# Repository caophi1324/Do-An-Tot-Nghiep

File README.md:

# Đồ Án Tốt Nghiệp

Workspace tổng hợp gồm 3 mảng chính: **phần cứng flight controller**, **mô phỏng bầy drone (SITL)** và **hệ thống nhận diện & bám sát khuôn mặt bằng AI**.

## Cấu trúc

| Thư mục | Nội dung |
|---|---|
| `Drone/` | Thiết kế phần cứng: flight controller `Drone ver2` (KiCad, BOM kèm LCSC), tay cầm điều khiển `Tay cam` (Altium), script tự động layout PCB (`Lib Kicad/arrange_*.py`), và 2 dự án tham khảo clone từ GitHub (`ESC_4in1_G071_1S3_SIZ200`, `Open-ESPilot`) |
| `drone_swarm_simulation_win11_wsl/` | Mô phỏng bầy drone ArduPilot SITL trên WSL: ứng dụng GCS (PySide6), engine ORCA/RVO2 + APF, điều khiển bằng gamepad, tích hợp Gazebo/RViz2. Hướng dẫn chạy: `HD_CHAY_MOPHONG_WIN11_WSL.md` |
| `StackMod/` | AI Face Tracking Studio: pipeline nhận diện khuôn mặt (YOLO + RetinaFace + EdgeFace + eDifFIQA), UI PySide6, REST API FastAPI, Docker. Hướng dẫn: `StackMod/README.md` |
| `fimware skill/` | Bộ 8 skill `.skill` (hướng dẫn vận hành drone: bringup, flight-safety, log-review, mavlink-review, sitl-sim, tuning...) kèm manifest SHA256 |

## Nội dung KHÔNG đưa lên repo (giữ trên máy local)

- `Drone/LIb AL/` — thư viện Altium cá nhân, các file >100 MB vượt giới hạn GitHub.
- `Drone/Lib Kicad/kicad-footprints`, `kicad-symbols-master` — thư viện chuẩn KiCad, cài lại qua KiCad hoặc clone từ [KiCad gitlab](https://gitlab.com/kicad).
- `drone_swarm_simulation_win11_wsl/ardupilot_wiki/` — clone wiki ArduPilot (~2.2 GB), xem [ArduPilot/ardupilot_wiki](https://github.com/ArduPilot/ardupilot_wiki).
- `StackMod/data/` — database + ảnh snapshots sinh khi chạy (chứa dữ liệu khuôn mặt).
- `StackMod/.venv/` — môi trường ảo Python.
- Các file `.zip`/`.rar` — bản nén trùng với nội dung đã giải nén.

## Ghi chú về các repo git cũ (`.git.bak`)

Các thư mục con trước đây có repo git riêng (`StackMod`, `Drone/ESC_4in1_G071_1S3_SIZ200`, `Drone/Open-ESPilot`, `Drone/Tay cam`) đã được gộp nội dung vào repo này; thư mục `.git` cũ được đổi tên thành `.git.bak` (bị gitignore). Muốn khôi phục repo riêng cũ, đổi tên `.git.bak` trở lại thành `.git`.

## Cài đặt nhanh StackMod

```bash
cd StackMod
python -m venv .venv && .venv\Scripts\activate
pip install -e .
python tools/download_models.py   # nếu chưa có models/*.onnx
```

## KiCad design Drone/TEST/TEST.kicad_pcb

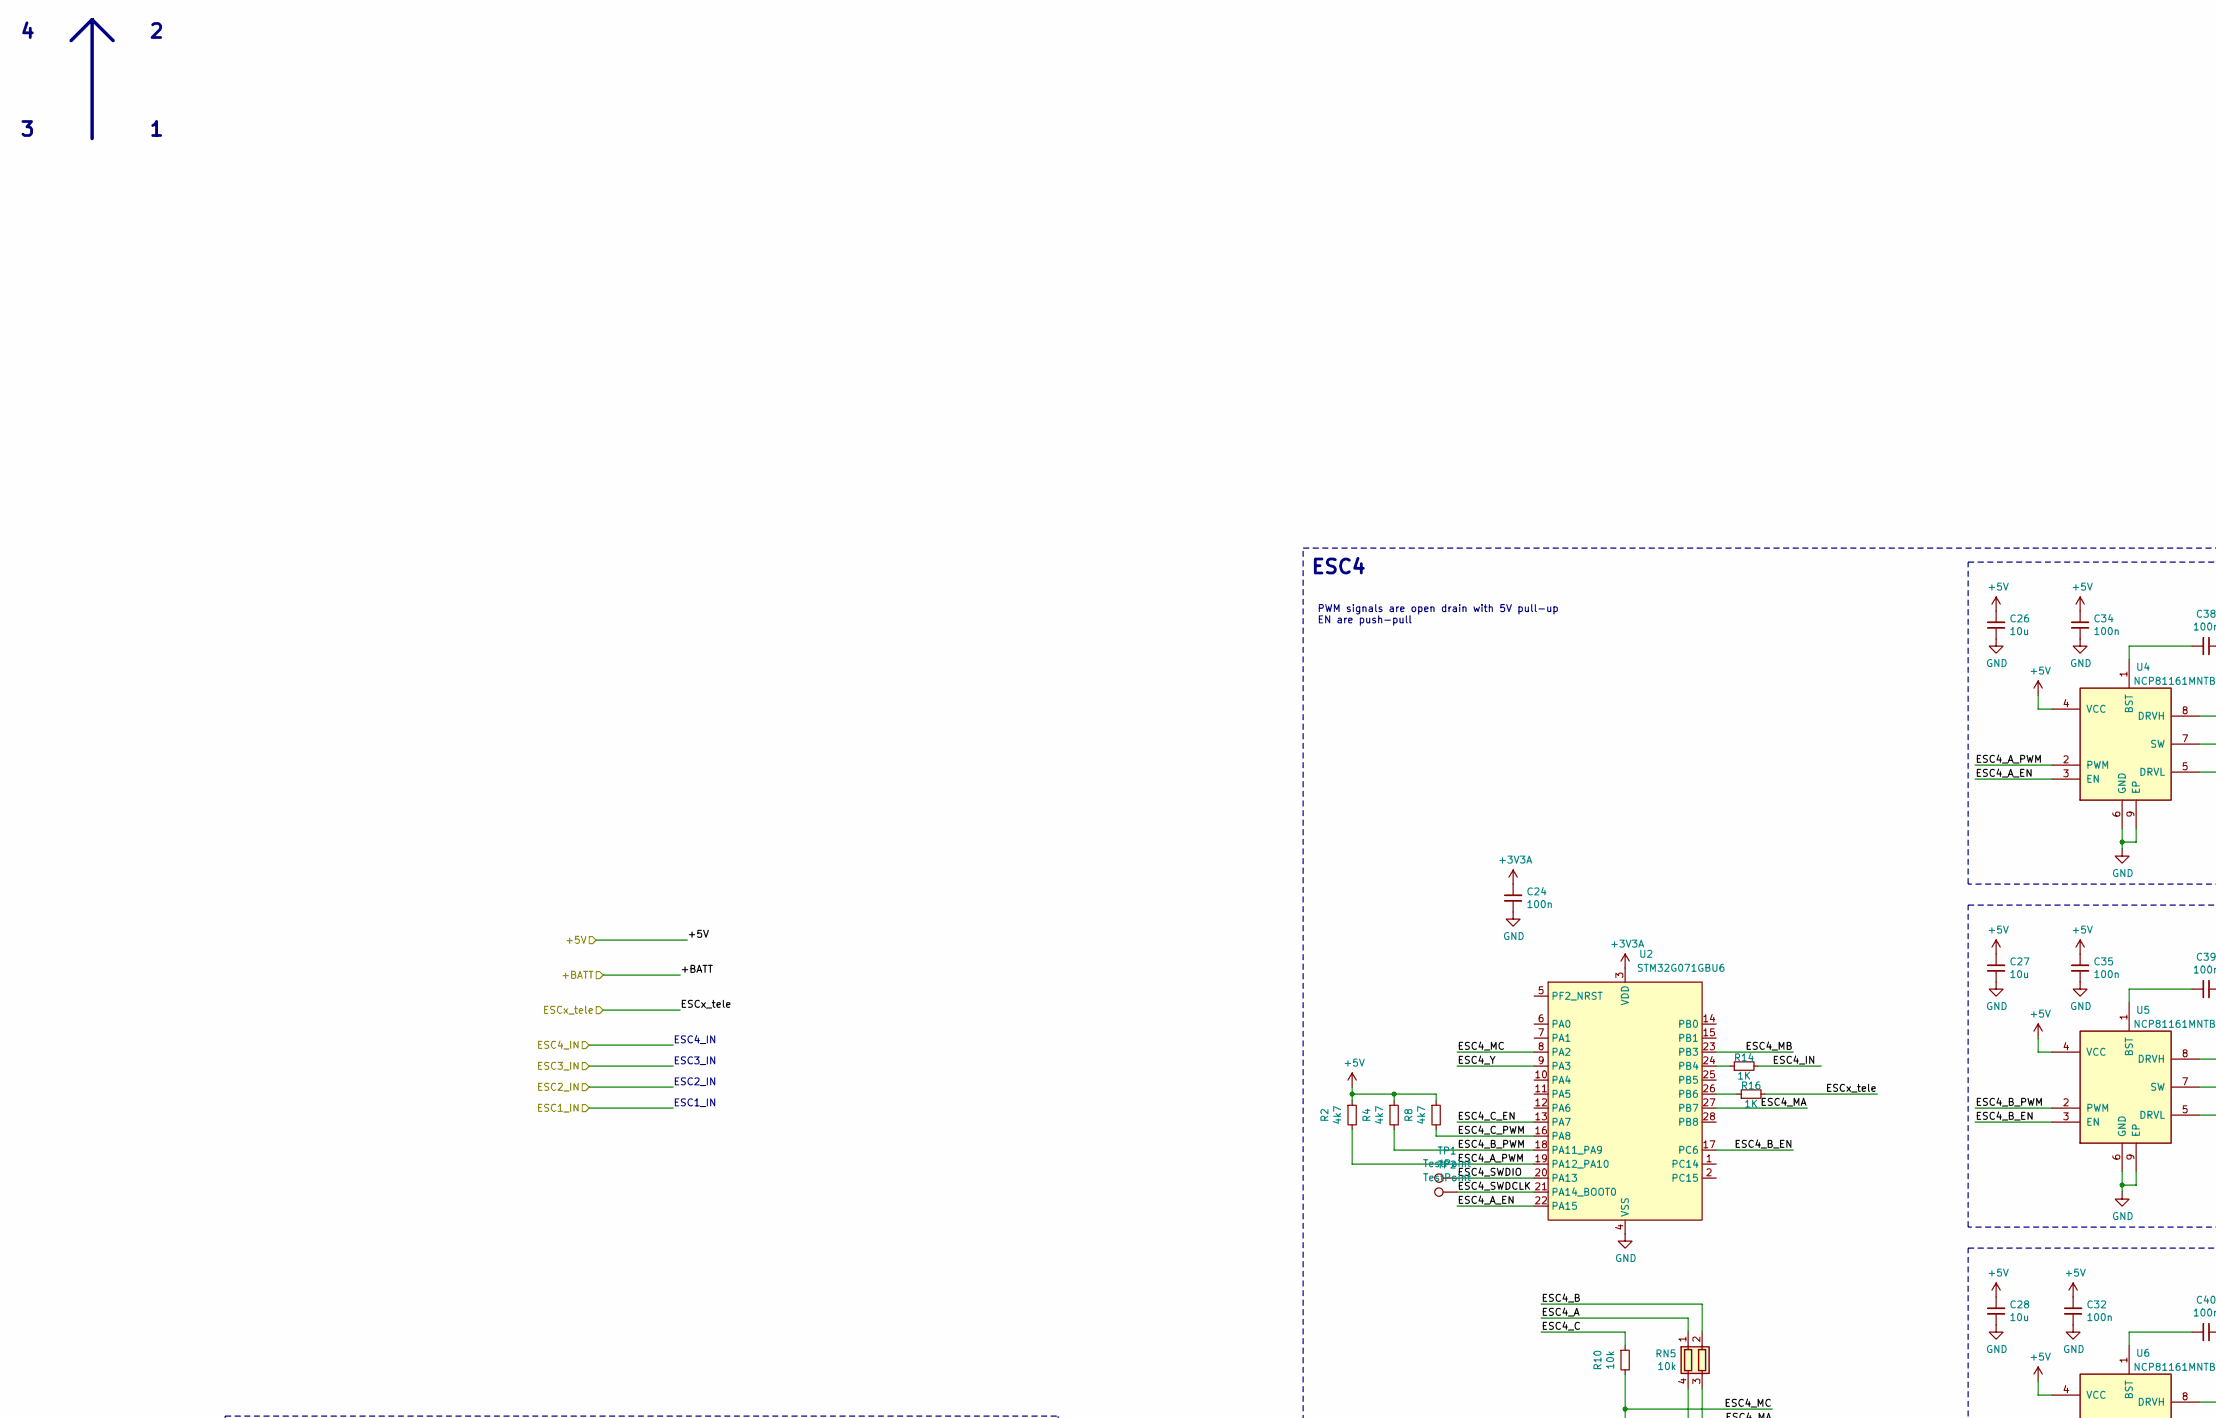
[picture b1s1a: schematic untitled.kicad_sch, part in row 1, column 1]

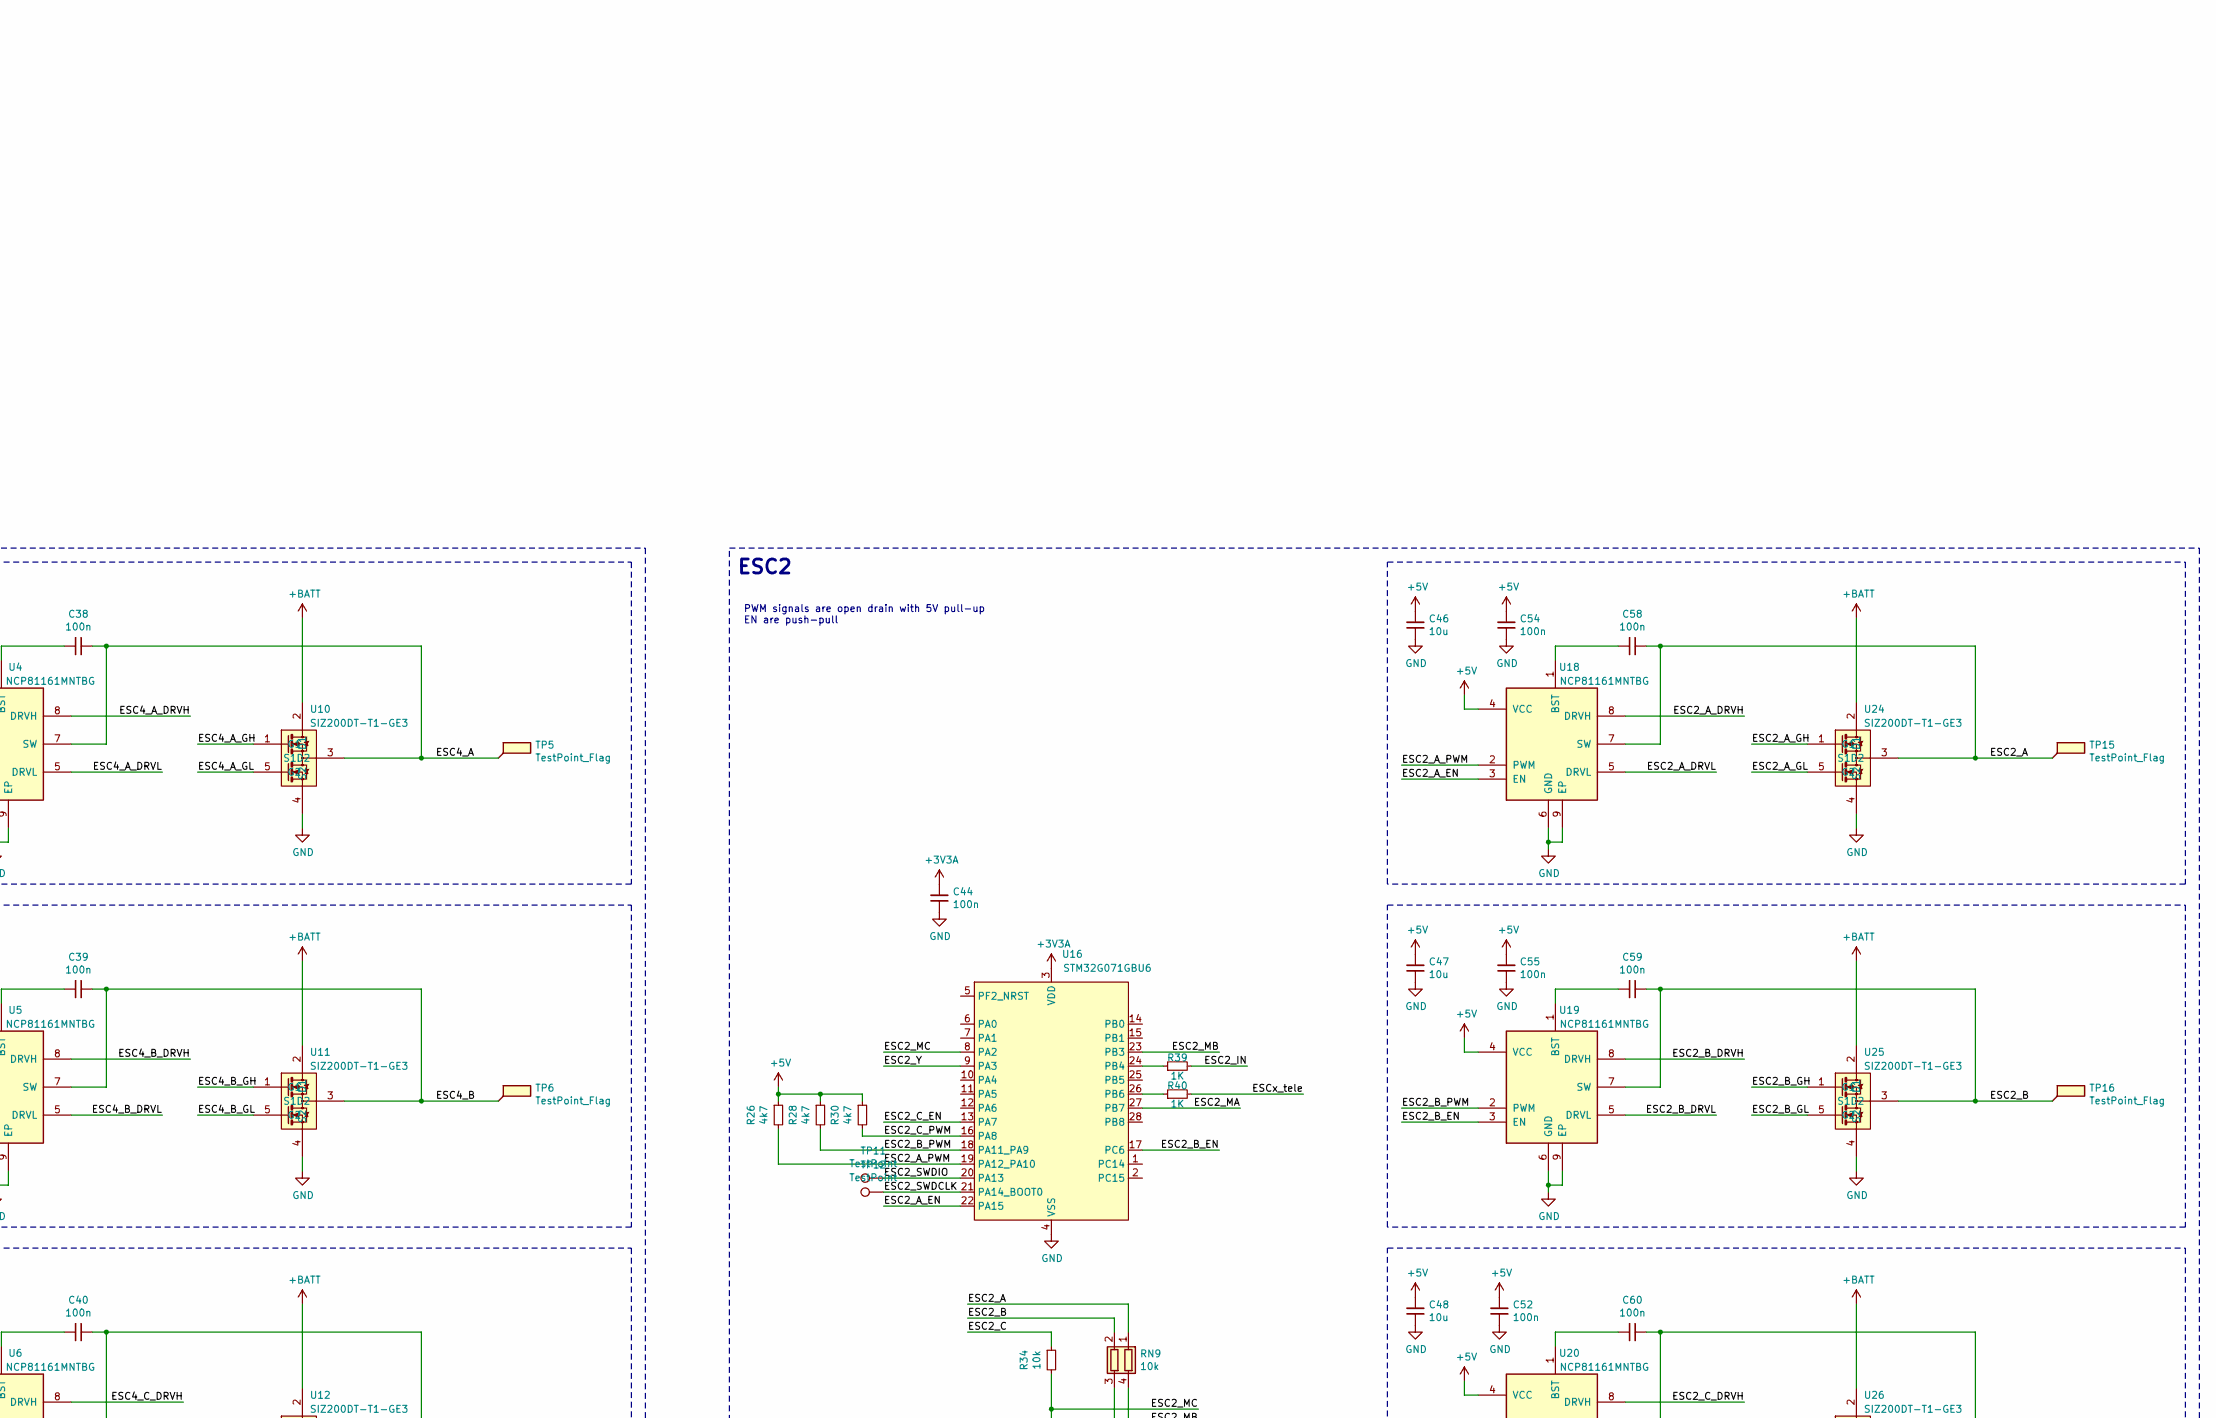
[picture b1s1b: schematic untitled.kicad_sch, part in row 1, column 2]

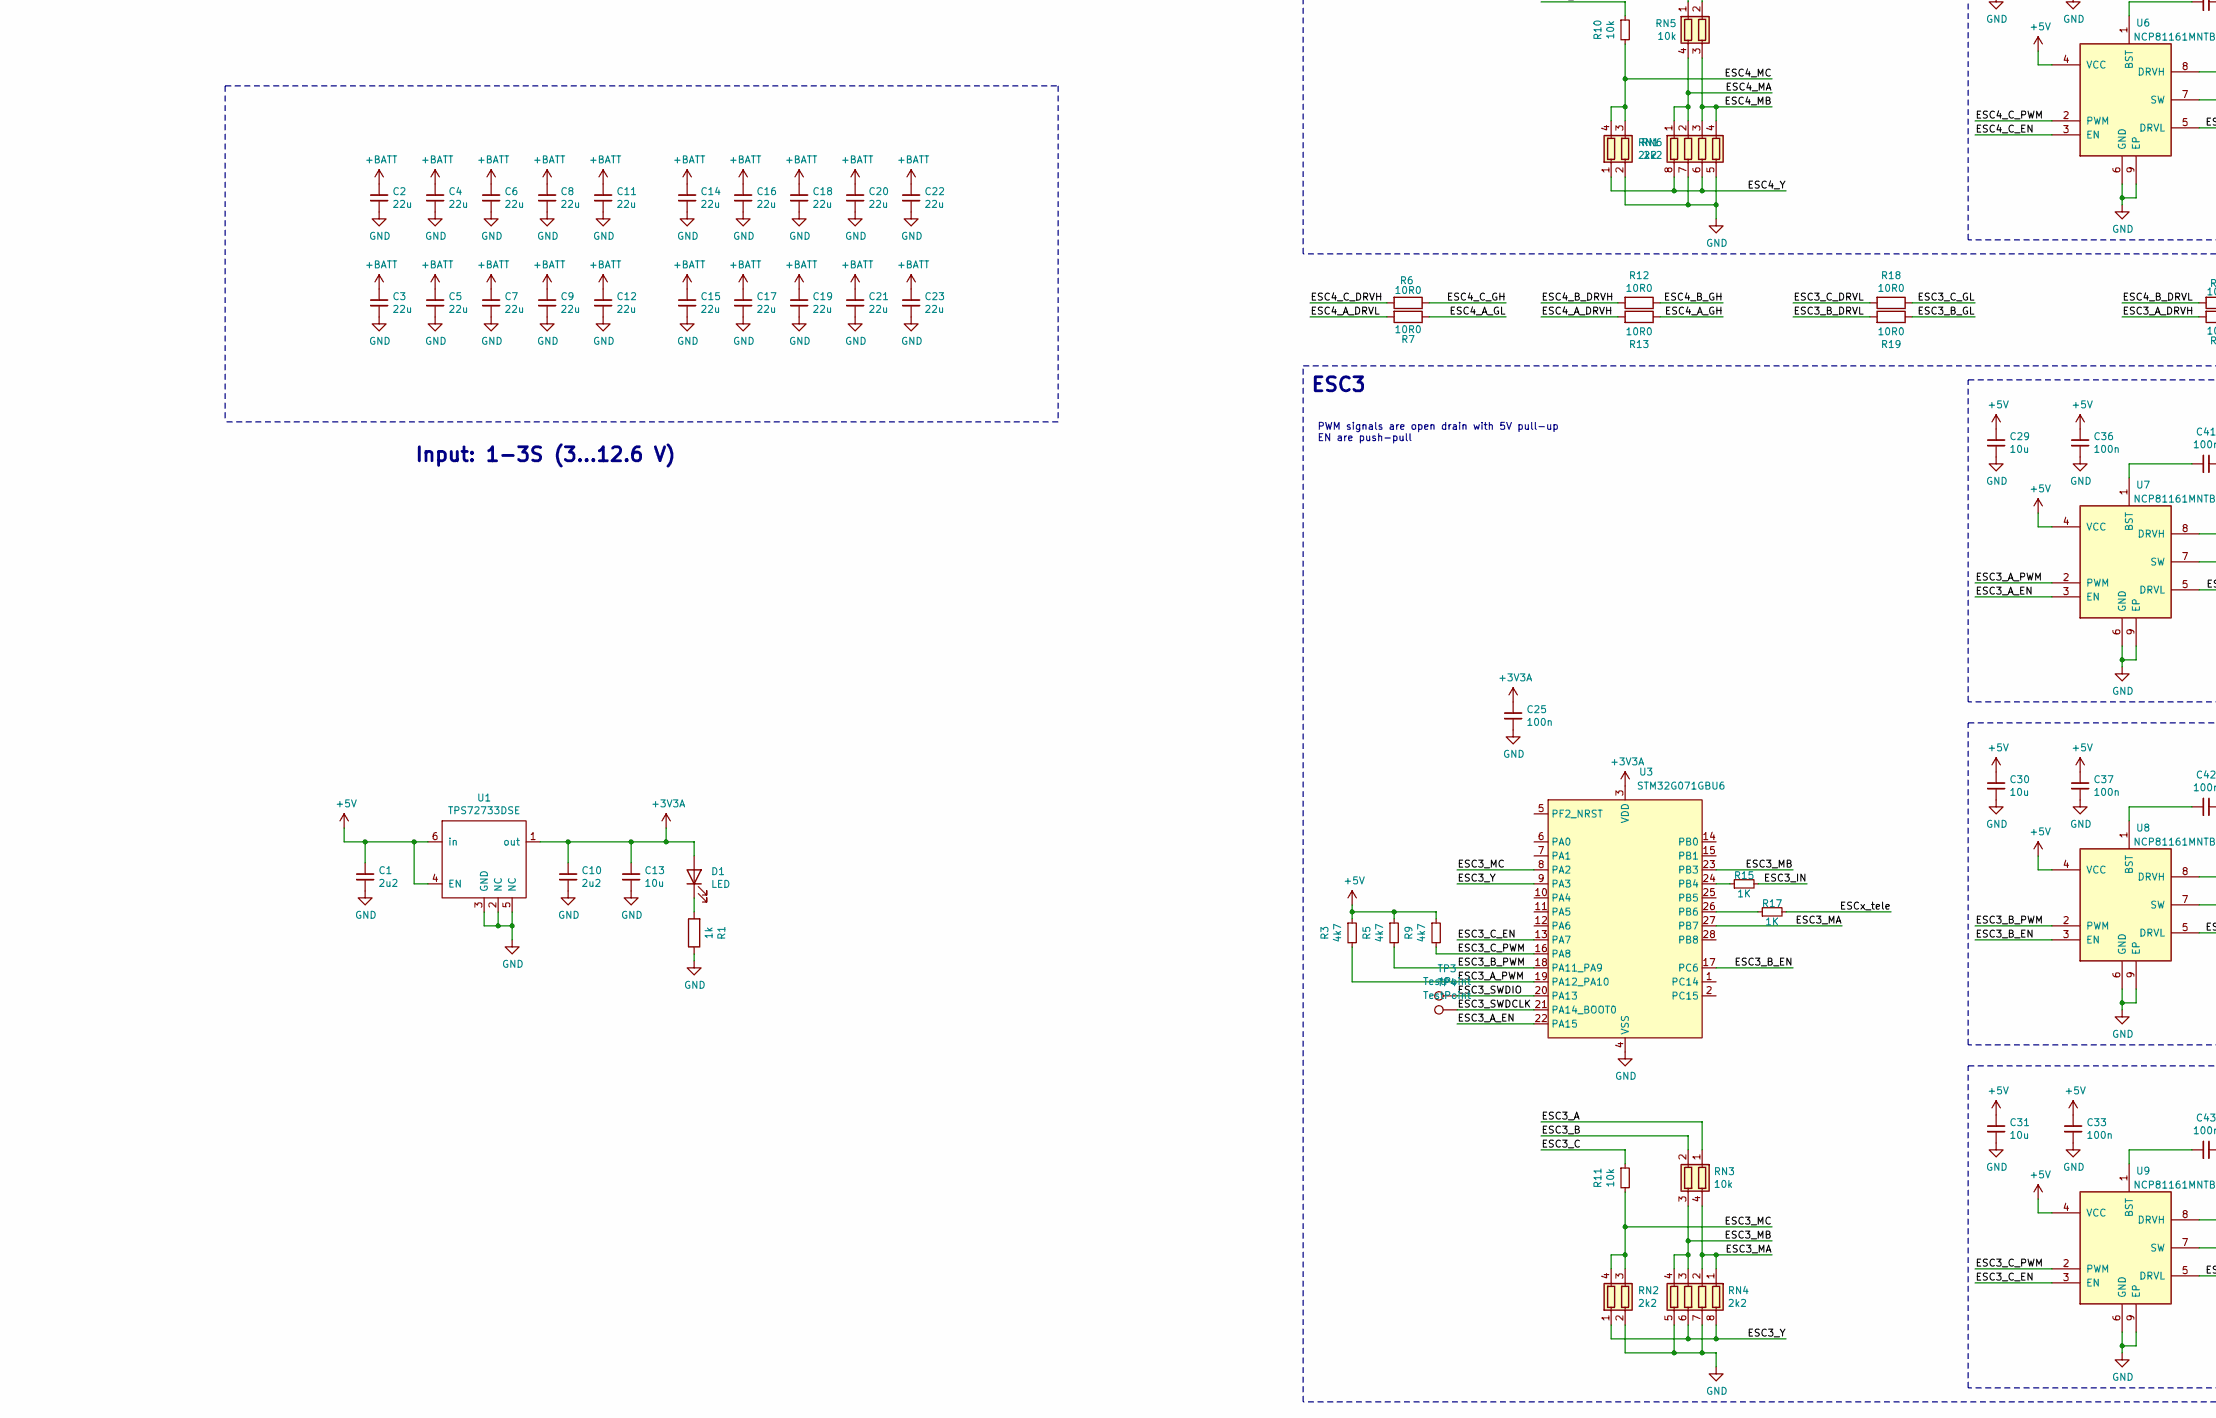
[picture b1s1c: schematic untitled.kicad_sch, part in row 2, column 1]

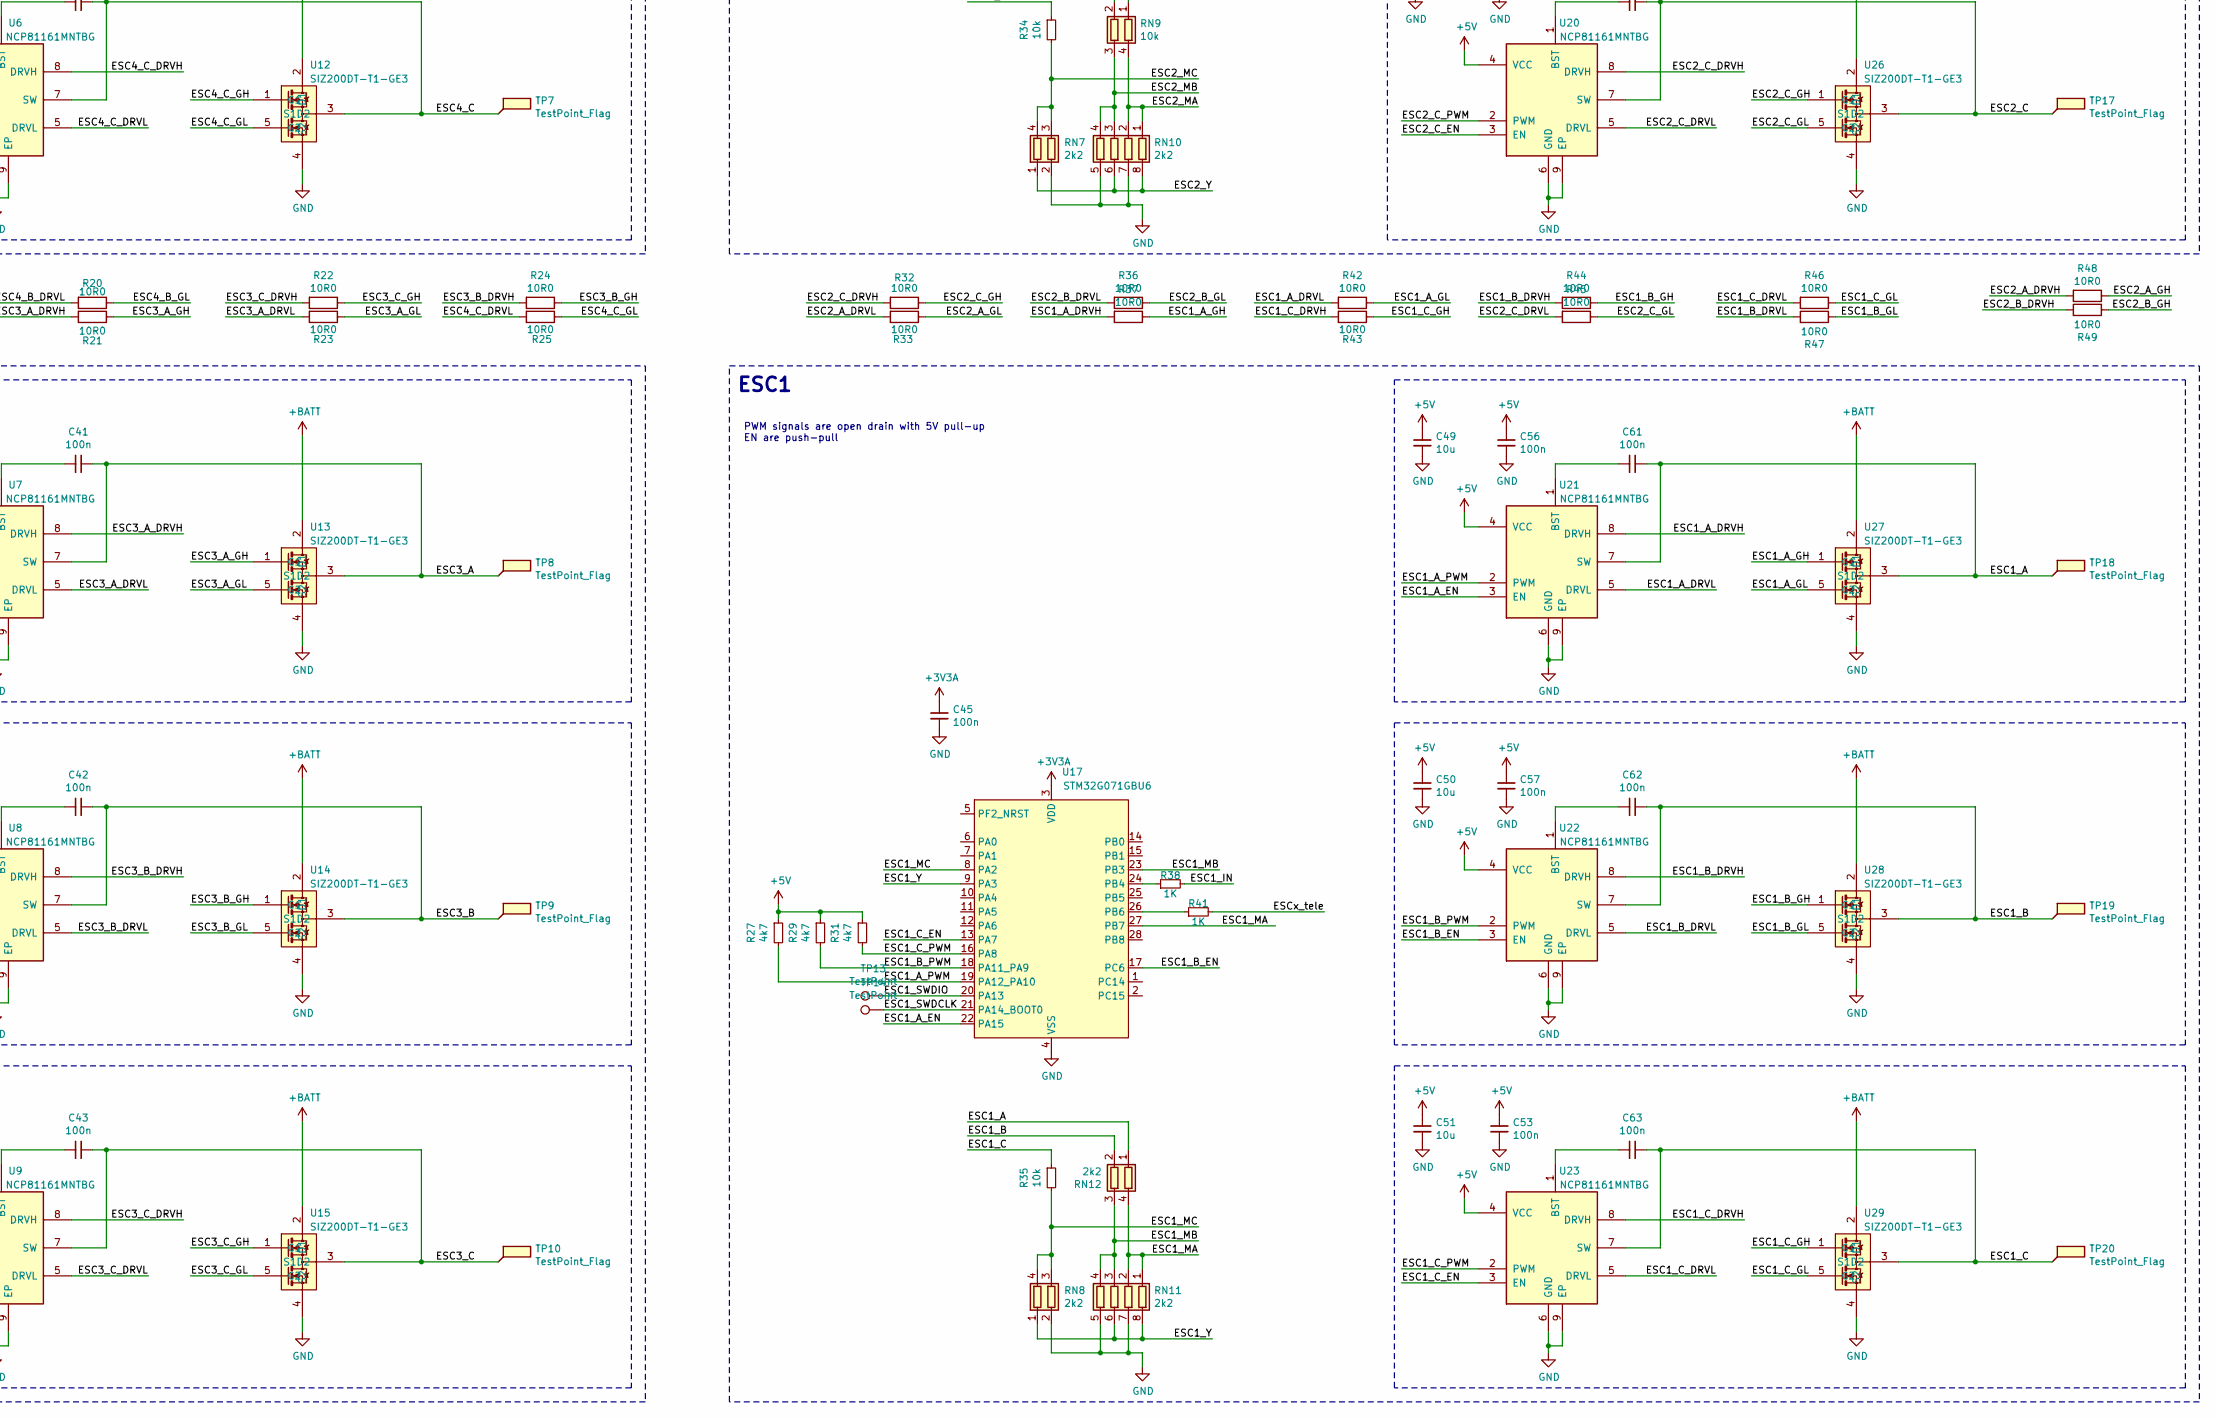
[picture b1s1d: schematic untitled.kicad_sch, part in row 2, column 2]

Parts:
C1, C10: 2u2; C_0402_1005Metric
C2, C3, C4, C5, C6, C7, C8, C9, C11, C12, C14, C15, C16, C17, C18, C19, C20, C21, C22, C23: 22u; C_0805_2012Metric_dense
C13, C26, C27, C28, C29, C30, C31, C46, C47, C48, C49, C50, C51: 10u; C_0402_1005Metric
C24, C25, C32, C33, C34, C35, C36, C37, C38, C39, C40, C41, C42, C43, C44, C45, C52, C53, C54, C55, C56, C57, C58, C59, C60, C61, C62, C63: 100n; C_0402_1005Metric
D1: LED; LED_0603_1608Metric
R1: 1k; R_0402_1005Metric
R2, R3, R4, R5, R8, R9, R26, R27, R28, R29, R30, R31: 4k7; R_0402_1005Metric
R6, R7, R12, R13, R18, R19, R20, R21, R22, R23, R24, R25, R32, R33, R36, R37, R42, R43, R44, R45, R46, R47, R48, R49: 10R0; R_0402_1005Metric
R10, R11, R34, R35: 10k; R_0402_1005Metric
R14, R15, R16, R17, R38, R39, R40, R41: 1K; R_0402_1005Metric
RN1, RN2, RN7, RN8: 2k2; R_Array_Convex_2x0402_dense
RN3, RN5, RN9: 10k; R_Array_Convex_2x0402_dense
RN4, RN6, RN10, RN11: 2k2; R_Array_Convex_4x0402_dense
RN12: 2k2; R_Array_Convex_2x0402
TP1, TP2, TP3, TP4, TP11, TP12, TP13, TP14: TestPoint; TestPoint_Pad_D1.0mm_dense
TP5, TP6, TP7, TP8, TP9, TP10, TP15, TP16, TP17, TP18, TP19, TP20: TestPoint_Flag; esc_pad_relaxed_n4
U1: TPS72733DSE; WSON-6_1.5x1.5mm_P0.5mm
U2, U3, U16, U17: STM32G071GBU6; UFQFPN28
U4, U5, U6, U7, U8, U9, U18, U19, U20, U21, U22, U23: NCP81161MNTBG; DFN-8-1EP_2x2mm_P0.5mm_EP0.9x1.3mm_narrow
U10, U11, U12, U13, U14, U15, U24, U25, U26, U27, U28, U29: SIZ200DT-T1-GE3; PowerPAIR3.3x3.3_splitpaste

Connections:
+3V3A: C10.2, C13.2, C24.2, C25.2, C44.2, C45.2, D1.2 (A), U1.1 (out), U2.3 (VDD), U3.3 (VDD), U16.3 (VDD), U17.3 (VDD)
+5V: C1.2, C26.2, C27.2, C28.2, C29.2, C30.2, C31.2, C32.2, C33.2, C34.2, C35.2, C36.2, C37.2, C46.2, C47.2, C48.2, C49.2, C50.2, C51.2, C52.2, C53.2, C54.2, C55.2, C56.2, C57.2, R2.1, R3.1, R4.1, R5.1, R8.1, R9.1, R26.1, R27.1, R28.1, R29.1, R30.1, R31.1, U1.4 (EN), U1.6 (in), U4.4 (VCC), U5.4 (VCC), U6.4 (VCC), U7.4 (VCC), U8.4 (VCC), U9.4 (VCC), U18.4 (VCC), U19.4 (VCC), U20.4 (VCC), U21.4 (VCC), U22.4 (VCC), U23.4 (VCC); also elsewhere on the board
+BATT: C2.2, C3.2, C4.2, C5.2, C6.2, C7.2, C8.2, C9.2, C11.2, C12.2, C14.2, C15.2, C16.2, C17.2, C18.2, C19.2, C20.2, C21.2, C22.2, C23.2, U10.2 (D1), U11.2 (D1), U12.2 (D1), U13.2 (D1), U14.2 (D1), U15.2 (D1), U24.2 (D1), U25.2 (D1), U26.2 (D1), U27.2 (D1), U28.2 (D1), U29.2 (D1); also elsewhere on the board
/ESC/ESC1_A: C61.1, RN12.1 (R1.1), TP18.1 (1_1), U21.7 (SW), U27.3 (S1D2)
/ESC/ESC1_A_DRVH: R37.2, U21.8 (DRVH)
/ESC/ESC1_A_DRVL: R42.2, U21.5 (DRVL)
/ESC/ESC1_A_EN: U17.22 (PA15), U21.3 (EN)
/ESC/ESC1_A_GH: R37.1, U27.1 (G1)
/ESC/ESC1_A_GL: R42.1, U27.5 (G2)
/ESC/ESC1_A_PWM: R27.2, U17.19 (PA12_PA10), U21.2 (PWM)
/ESC/ESC1_B: C62.1, RN12.2 (R2.1), TP19.1 (1_1), U22.7 (SW), U28.3 (S1D2)
/ESC/ESC1_B_DRVH: R44.2, U22.8 (DRVH)
/ESC/ESC1_B_DRVL: R47.2, U22.5 (DRVL)
/ESC/ESC1_B_EN: U17.17 (PC6), U22.3 (EN)
/ESC/ESC1_B_GH: R44.1, U28.1 (G1)
/ESC/ESC1_B_GL: R47.1, U28.5 (G2)
/ESC/ESC1_B_PWM: R29.2, U17.18 (PA11_PA9), U22.2 (PWM)
/ESC/ESC1_C: C63.1, R35.1, TP20.1 (1_1), U23.7 (SW), U29.3 (S1D2)
/ESC/ESC1_C_DRVH: R43.2, U23.8 (DRVH)
/ESC/ESC1_C_DRVL: R46.2, U23.5 (DRVL)
/ESC/ESC1_C_EN: U17.13 (PA7), U23.3 (EN)
/ESC/ESC1_C_GH: R43.1, U29.1 (G1)
/ESC/ESC1_C_GL: R46.1, U29.5 (G2)
/ESC/ESC1_C_PWM: R31.2, U17.16 (PA8), U23.2 (PWM)
/ESC/ESC1_IN: R38.2; also elsewhere on the board
/ESC/ESC1_MA: RN11.1 (R1.1), RN11.2 (R2.1), RN12.4 (R1.2), U17.27 (PB7)
/ESC/ESC1_MB: RN11.3 (R3.1), RN11.4 (R4.1), RN12.3 (R2.2), U17.23 (PB3)
/ESC/ESC1_MC: R35.2, RN8.3 (R2.2), RN8.4 (R1.2), U17.8 (PA2)
/ESC/ESC1_SWDCLK: TP14.1 (1_1), U17.21 (PA14_BOOT0)
/ESC/ESC1_SWDIO: TP13.1 (1_1), U17.20 (PA13)
/ESC/ESC1_Y: RN8.1 (R1.1), RN11.6 (R3.2), RN11.8 (R1.2), U17.9 (PA3)
/ESC/ESC2_A: C58.1, RN9.1 (R1.1), TP15.1 (1_1), U18.7 (SW), U24.3 (S1D2)
/ESC/ESC2_A_DRVH: R48.2, U18.8 (DRVH)
/ESC/ESC2_A_DRVL: R33.2, U18.5 (DRVL)
/ESC/ESC2_A_EN: U16.22 (PA15), U18.3 (EN)
/ESC/ESC2_A_GH: R48.1, U24.1 (G1)
/ESC/ESC2_A_GL: R33.1, U24.5 (G2)
/ESC/ESC2_A_PWM: R26.2, U16.19 (PA12_PA10), U18.2 (PWM)
/ESC/ESC2_B: C59.1, RN9.2 (R2.1), TP16.1 (1_1), U19.7 (SW), U25.3 (S1D2)
/ESC/ESC2_B_DRVH: R49.2, U19.8 (DRVH)
/ESC/ESC2_B_DRVL: R36.2, U19.5 (DRVL)
/ESC/ESC2_B_EN: U16.17 (PC6), U19.3 (EN)
/ESC/ESC2_B_GH: R49.1, U25.1 (G1)
/ESC/ESC2_B_GL: R36.1, U25.5 (G2)
/ESC/ESC2_B_PWM: R28.2, U16.18 (PA11_PA9), U19.2 (PWM)
/ESC/ESC2_C: C60.1, R34.1, TP17.1 (1_1), U20.7 (SW), U26.3 (S1D2)
/ESC/ESC2_C_DRVH: R32.2, U20.8 (DRVH)
/ESC/ESC2_C_DRVL: R45.2, U20.5 (DRVL)
/ESC/ESC2_C_EN: U16.13 (PA7), U20.3 (EN)
/ESC/ESC2_C_GH: R32.1, U26.1 (G1)
/ESC/ESC2_C_GL: R45.1, U26.5 (G2)
/ESC/ESC2_C_PWM: R30.2, U16.16 (PA8), U20.2 (PWM)
/ESC/ESC2_IN: R39.2; also elsewhere on the board
/ESC/ESC2_MA: RN9.4 (R1.2), RN10.1 (R1.1), RN10.2 (R2.1), U16.27 (PB7)
/ESC/ESC2_MB: RN9.3 (R2.2), RN10.3 (R3.1), RN10.4 (R4.1), U16.23 (PB3)
/ESC/ESC2_MC: R34.2, RN7.3 (R2.2), RN7.4 (R1.2), U16.8 (PA2)
/ESC/ESC2_SWDCLK: TP12.1 (1_1), U16.21 (PA14_BOOT0)
/ESC/ESC2_SWDIO: TP11.1 (1_1), U16.20 (PA13)
/ESC/ESC2_Y: RN7.1 (R1.1), RN10.6 (R3.2), RN10.8 (R1.2), U16.9 (PA3)
/ESC/ESC3_A: C41.1, RN3.1 (R1.1), TP8.1 (1_1), U7.7 (SW), U13.3 (S1D2)
/ESC/ESC3_A_DRVH: R21.2, U7.8 (DRVH)
/ESC/ESC3_A_DRVL: R23.2, U7.5 (DRVL)
/ESC/ESC3_A_EN: U3.22 (PA15), U7.3 (EN)
/ESC/ESC3_A_GH: R21.1, U13.1 (G1)
/ESC/ESC3_A_GL: R23.1, U13.5 (G2)
/ESC/ESC3_A_PWM: R3.2, U3.19 (PA12_PA10), U7.2 (PWM)
/ESC/ESC3_B: C42.1, RN3.2 (R2.1), TP9.1 (1_1), U8.7 (SW), U14.3 (S1D2)
/ESC/ESC3_B_DRVH: R24.2, U8.8 (DRVH)
/ESC/ESC3_B_DRVL: R19.2, U8.5 (DRVL)
/ESC/ESC3_B_EN: U3.17 (PC6), U8.3 (EN)
/ESC/ESC3_B_GH: R24.1, U14.1 (G1)
/ESC/ESC3_B_GL: R19.1, U14.5 (G2)
/ESC/ESC3_B_PWM: R5.2, U3.18 (PA11_PA9), U8.2 (PWM)
/ESC/ESC3_C: C43.1, R11.1, TP10.1 (1_1), U9.7 (SW), U15.3 (S1D2)
/ESC/ESC3_C_DRVH: R22.2, U9.8 (DRVH)
/ESC/ESC3_C_DRVL: R18.2, U9.5 (DRVL)
/ESC/ESC3_C_EN: U3.13 (PA7), U9.3 (EN)
/ESC/ESC3_C_GH: R22.1, U15.1 (G1)
/ESC/ESC3_C_GL: R18.1, U15.5 (G2)
/ESC/ESC3_C_PWM: R9.2, U3.16 (PA8), U9.2 (PWM)
/ESC/ESC3_IN: R15.2; also elsewhere on the board
/ESC/ESC3_MA: RN3.4 (R1.2), RN4.1 (R1.1), RN4.2 (R2.1), U3.27 (PB7)
/ESC/ESC3_MB: RN3.3 (R2.2), RN4.3 (R3.1), RN4.4 (R4.1), U3.23 (PB3)
/ESC/ESC3_MC: R11.2, RN2.3 (R2.2), RN2.4 (R1.2), U3.8 (PA2)
/ESC/ESC3_SWDCLK: TP4.1 (1_1), U3.21 (PA14_BOOT0)
/ESC/ESC3_SWDIO: TP3.1 (1_1), U3.20 (PA13)
/ESC/ESC3_Y: RN2.1 (R1.1), RN4.6 (R3.2), RN4.8 (R1.2), U3.9 (PA3)
/ESC/ESC4_A: C38.1, RN5.1 (R1.1), TP5.1 (1_1), U4.7 (SW), U10.3 (S1D2)
/ESC/ESC4_A_DRVH: R13.2, U4.8 (DRVH)
/ESC/ESC4_A_DRVL: R7.2, U4.5 (DRVL)
/ESC/ESC4_A_EN: U2.22 (PA15), U4.3 (EN)
/ESC/ESC4_A_GH: R13.1, U10.1 (G1)
/ESC/ESC4_A_GL: R7.1, U10.5 (G2)
/ESC/ESC4_A_PWM: R2.2, U2.19 (PA12_PA10), U4.2 (PWM)
/ESC/ESC4_B: C39.1, RN5.2 (R2.1), TP6.1 (1_1), U5.7 (SW), U11.3 (S1D2)
/ESC/ESC4_B_DRVH: R12.2, U5.8 (DRVH)
/ESC/ESC4_B_DRVL: R20.2, U5.5 (DRVL)
/ESC/ESC4_B_EN: U2.17 (PC6), U5.3 (EN)
/ESC/ESC4_B_GH: R12.1, U11.1 (G1)
/ESC/ESC4_B_GL: R20.1, U11.5 (G2)
/ESC/ESC4_B_PWM: R4.2, U2.18 (PA11_PA9), U5.2 (PWM)
/ESC/ESC4_C: C40.1, R10.1, TP7.1 (1_1), U6.7 (SW), U12.3 (S1D2)
/ESC/ESC4_C_DRVH: R6.2, U6.8 (DRVH)
/ESC/ESC4_C_DRVL: R25.2, U6.5 (DRVL)
/ESC/ESC4_C_EN: U2.13 (PA7), U6.3 (EN)
/ESC/ESC4_C_GH: R6.1, U12.1 (G1)
/ESC/ESC4_C_GL: R25.1, U12.5 (G2)
/ESC/ESC4_C_PWM: R8.2, U2.16 (PA8), U6.2 (PWM)
/ESC/ESC4_IN: R14.2; also elsewhere on the board
/ESC/ESC4_MA: RN5.4 (R1.2), RN6.1 (R1.1), RN6.2 (R2.1), U2.27 (PB7)
/ESC/ESC4_MB: RN5.3 (R2.2), RN6.3 (R3.1), RN6.4 (R4.1), U2.23 (PB3)
/ESC/ESC4_MC: R10.2, RN1.3 (R2.2), RN1.4 (R1.2), U2.8 (PA2)
/ESC/ESC4_SWDCLK: TP2.1 (1_1), U2.21 (PA14_BOOT0)
/ESC/ESC4_SWDIO: TP1.1 (1_1), U2.20 (PA13)
/ESC/ESC4_Y: RN1.1 (R1.1), RN6.6 (R3.2), RN6.8 (R1.2), U2.9 (PA3)
/ESC/ESCx_tele: R16.2, R17.2, R40.2, R41.2; also elsewhere on the board
GND: C1.1, C2.1, C3.1, C4.1, C5.1, C6.1, C7.1, C8.1, C9.1, C10.1, C11.1, C12.1, C13.1, C14.1, C15.1, C16.1, C17.1, C18.1, C19.1, C20.1, C21.1, C22.1, C23.1, C24.1, C25.1, C26.1, C27.1, C28.1, C29.1, C30.1, C31.1, C32.1, C33.1, C34.1, C35.1, C36.1, C37.1, C44.1, C45.1, C46.1, C47.1, C48.1, C49.1, C50.1, C51.1, C52.1, C53.1, C54.1, C55.1, C56.1, C57.1, R1.1, RN1.2 (R2.1), RN2.2 (R2.1), RN4.5 (R4.2), RN4.7 (R2.2), RN6.5 (R4.2), RN6.7 (R2.2), RN7.2 (R2.1), RN8.2 (R2.1), RN10.5 (R4.2), RN10.7 (R2.2), RN11.5 (R4.2), RN11.7 (R2.2), U1.2 (NC), U1.3 (GND), U1.5 (NC), U2.4 (VSS), U3.4 (VSS), U4.6 (GND), U4.9 (EP), U5.6 (GND), U5.9 (EP), U6.6 (GND), U6.9 (EP), U7.6 (GND), U7.9 (EP), U8.6 (GND), U8.9 (EP), U9.6 (GND), U9.9 (EP), U10.4 (S2), U11.4 (S2), U12.4 (S2), U13.4 (S2), U14.4 (S2), U15.4 (S2), U16.4 (VSS), U17.4 (VSS), U18.6 (GND), U18.9 (EP), U19.6 (GND), U19.9 (EP), U20.6 (GND), U20.9 (EP), U21.6 (GND), U21.9 (EP), U22.6 (GND), U22.9 (EP), U23.6 (GND), U23.9 (EP), U24.4 (S2), U25.4 (S2), U26.4 (S2), U27.4 (S2), U28.4 (S2), U29.4 (S2); also elsewhere on the board
unnamed: D1.1 (K), R1.2
unnamed: R14.1, U2.24 (PB4)
unnamed: R16.1, U2.26 (PB6)
unnamed: R15.1, U3.24 (PB4)
unnamed: R17.1, U3.26 (PB6)
unnamed: C38.2, U4.1 (BST)
unnamed: C39.2, U5.1 (BST)
unnamed: C40.2, U6.1 (BST)
unnamed: C41.2, U7.1 (BST)
unnamed: C42.2, U8.1 (BST)
unnamed: C43.2, U9.1 (BST)
unnamed: R39.1, U16.24 (PB4)
unnamed: R40.1, U16.26 (PB6)
unnamed: R38.1, U17.24 (PB4)
unnamed: R41.1, U17.26 (PB6)
unnamed: C58.2, U18.1 (BST)
unnamed: C59.2, U19.1 (BST)
unnamed: C60.2, U20.1 (BST)
unnamed: C61.2, U21.1 (BST)
unnamed: C62.2, U22.1 (BST)
unnamed: C63.2, U23.1 (BST)

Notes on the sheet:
PWM signals are open drain with 5V pull-up EN are push-pull
Input: 1-3S (3...12.6 V)
ESC4
ESC1_IN
ESC2
ESC3_IN
ESC3
ESC2_IN
ESC1
ESC4_IN
